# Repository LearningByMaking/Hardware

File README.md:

# Hardware
The design files and documentation for the LbyM hardware

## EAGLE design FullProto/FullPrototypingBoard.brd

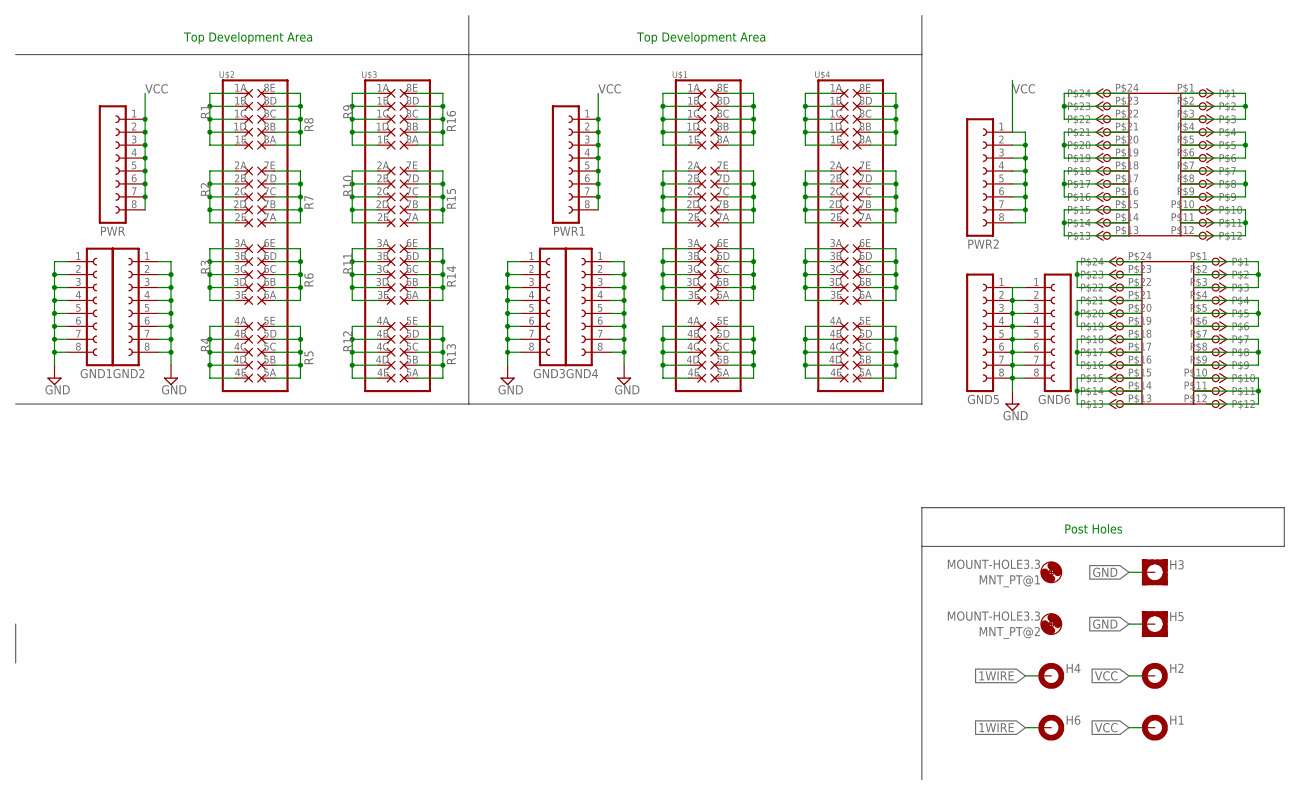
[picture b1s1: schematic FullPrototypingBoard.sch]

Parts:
GND1, GND2, GND3, GND4, GND5, GND6: FE08-GND
H1, H2, H4, H6: MOUNT-PAD-ROUND3.3; 3,3-PAD
H3, H5: MOUNT-PAD-SQUARE3.3; 3,3-PAD-SQUARE
MNT_PT@1, MNT_PT@2: MOUNT-HOLE3.3; 3,3
PWR, PWR1, PWR2: FE08
U$1, U$2, U$3, U$4: PROTO-5X8; PROTO-5X08
U$5, U$6: PROTO-3X8; PROTO-3X08

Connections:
1WIRE: H4.B3,3, H6.B3,3
GND: GND1.1, GND1.2, GND1.3, GND1.4, GND1.5, GND1.6, GND1.7, GND1.8, GND2.1, GND2.2, GND2.3, GND2.4, GND2.5, GND2.6, GND2.7, GND2.8, GND3.1, GND3.2, GND3.3, GND3.4, GND3.5, GND3.6, GND3.7, GND3.8, GND4.1, GND4.2, GND4.3, GND4.4, GND4.5, GND4.6, GND4.7, GND4.8, GND5.1, GND5.2, GND5.3, GND5.4, GND5.5, GND5.6, GND5.7, GND5.8, GND6.1, GND6.2, GND6.3, GND6.4, GND6.5, GND6.6, GND6.7, GND6.8, H3.B3,3, H5.B3,3
unnamed: U$5.P$22, U$5.P$23, U$5.P$24
unnamed: U$5.P$19, U$5.P$20, U$5.P$21
unnamed: U$5.P$16, U$5.P$17, U$5.P$18
unnamed: U$5.P$13, U$5.P$14, U$5.P$15
unnamed: U$5.P$1, U$5.P$2, U$5.P$3
unnamed: U$5.P$4, U$5.P$5, U$5.P$6
unnamed: U$5.P$7, U$5.P$8, U$5.P$9
unnamed: U$5.P$10, U$5.P$11
unnamed: U$6.P$22, U$6.P$23, U$6.P$24
unnamed: U$6.P$19, U$6.P$20, U$6.P$21
unnamed: U$6.P$16, U$6.P$17, U$6.P$18
unnamed: U$6.P$13, U$6.P$14, U$6.P$15
unnamed: U$6.P$1, U$6.P$2, U$6.P$3
unnamed: U$6.P$4, U$6.P$5, U$6.P$6
unnamed: U$6.P$7, U$6.P$8, U$6.P$9
unnamed: U$6.P$10, U$6.P$11
unnamed: U$1.1A, U$1.1B, U$1.1C, U$1.1D, U$1.1E
unnamed: U$1.8A, U$1.8B, U$1.8C, U$1.8D, U$1.8E
unnamed: U$1.7A, U$1.7B, U$1.7C, U$1.7D, U$1.7E
unnamed: U$1.2A, U$1.2B, U$1.2C, U$1.2D, U$1.2E
unnamed: U$1.6A, U$1.6B, U$1.6C, U$1.6D, U$1.6E
unnamed: U$1.3A, U$1.3B, U$1.3C, U$1.3D, U$1.3E
unnamed: U$1.5A, U$1.5B, U$1.5C, U$1.5D, U$1.5E
unnamed: U$1.4A, U$1.4B, U$1.4C, U$1.4D, U$1.4E
unnamed: U$4.8A, U$4.8B, U$4.8C, U$4.8D, U$4.8E
unnamed: U$4.1A, U$4.1B, U$4.1C, U$4.1D, U$4.1E
unnamed: U$4.7A, U$4.7B, U$4.7C, U$4.7D, U$4.7E
unnamed: U$4.2A, U$4.2B, U$4.2C, U$4.2D, U$4.2E
unnamed: U$4.6A, U$4.6B, U$4.6C, U$4.6D, U$4.6E
unnamed: U$4.3A, U$4.3B, U$4.3C, U$4.3D, U$4.3E
unnamed: U$4.5A, U$4.5B, U$4.5C, U$4.5D, U$4.5E
unnamed: U$4.4A, U$4.4B, U$4.4C, U$4.4D, U$4.4E
R1: U$2.1A, U$2.1B, U$2.1C, U$2.1D, U$2.1E
R2: U$2.2A, U$2.2B, U$2.2C, U$2.2D, U$2.2E
R3: U$2.3A, U$2.3B, U$2.3C, U$2.3D, U$2.3E
R4: U$2.4A, U$2.4B, U$2.4C, U$2.4D, U$2.4E
R5: U$2.5A, U$2.5B, U$2.5C, U$2.5D, U$2.5E
R6: U$2.6A, U$2.6B, U$2.6C, U$2.6D, U$2.6E
R7: U$2.7A, U$2.7B, U$2.7C, U$2.7D, U$2.7E
R8: U$2.8A, U$2.8B, U$2.8C, U$2.8D, U$2.8E
R9: U$3.1A, U$3.1B, U$3.1C, U$3.1D, U$3.1E
R10: U$3.2A, U$3.2B, U$3.2C, U$3.2D, U$3.2E
R11: U$3.3A, U$3.3B, U$3.3C, U$3.3D, U$3.3E
R12: U$3.4A, U$3.4B, U$3.4C, U$3.4D, U$3.4E
R13: U$3.5A, U$3.5B, U$3.5C, U$3.5D, U$3.5E
R14: U$3.6A, U$3.6B, U$3.6C, U$3.6D, U$3.6E
R15: U$3.7A, U$3.7B, U$3.7C, U$3.7D, U$3.7E
R16: U$3.8A, U$3.8B, U$3.8C, U$3.8D, U$3.8E
VCC: H1.B3,3, H2.B3,3, PWR.1, PWR.2, PWR.3, PWR.4, PWR.5, PWR.6, PWR.7, PWR.8, PWR1.1, PWR1.2, PWR1.3, PWR1.4, PWR1.5, PWR1.6, PWR1.7, PWR1.8, PWR2.1, PWR2.2, PWR2.3, PWR2.4, PWR2.5, PWR2.6, PWR2.7, PWR2.8

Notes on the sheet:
Post Holes
Top Development Area

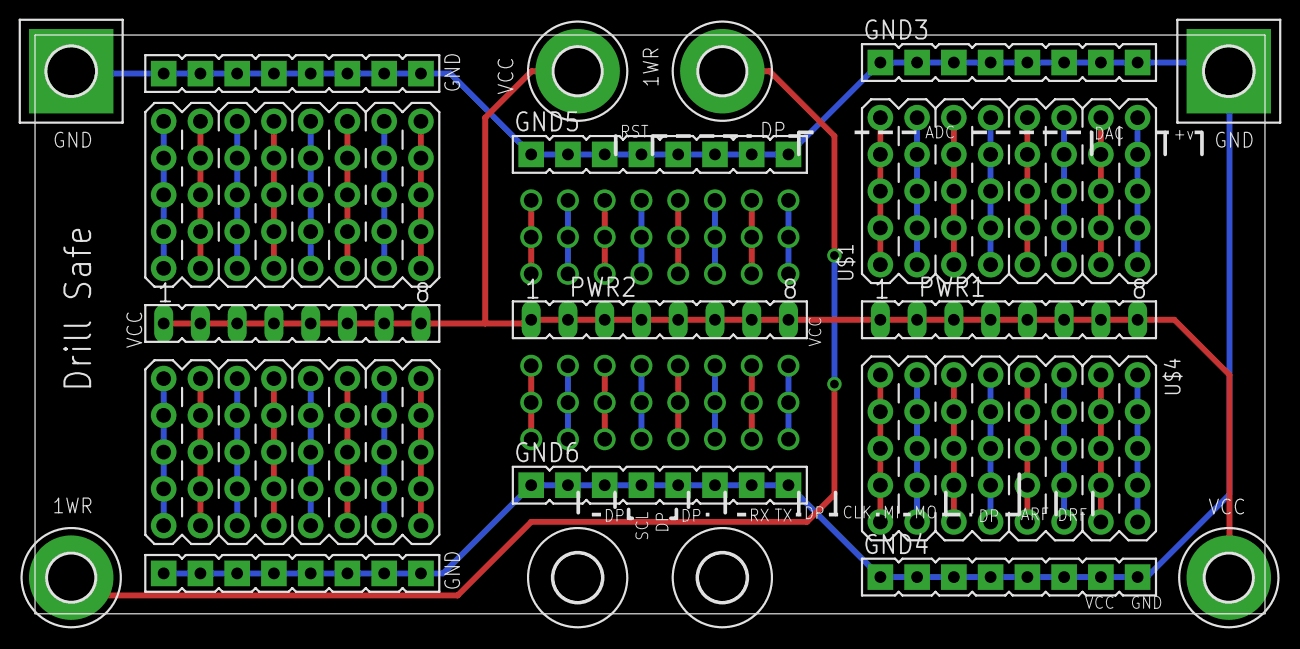
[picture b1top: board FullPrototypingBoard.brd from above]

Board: 2 copper layers, 85.0 x 40.0 mm, 23 parts (0 on the bottom side), 51 nets.

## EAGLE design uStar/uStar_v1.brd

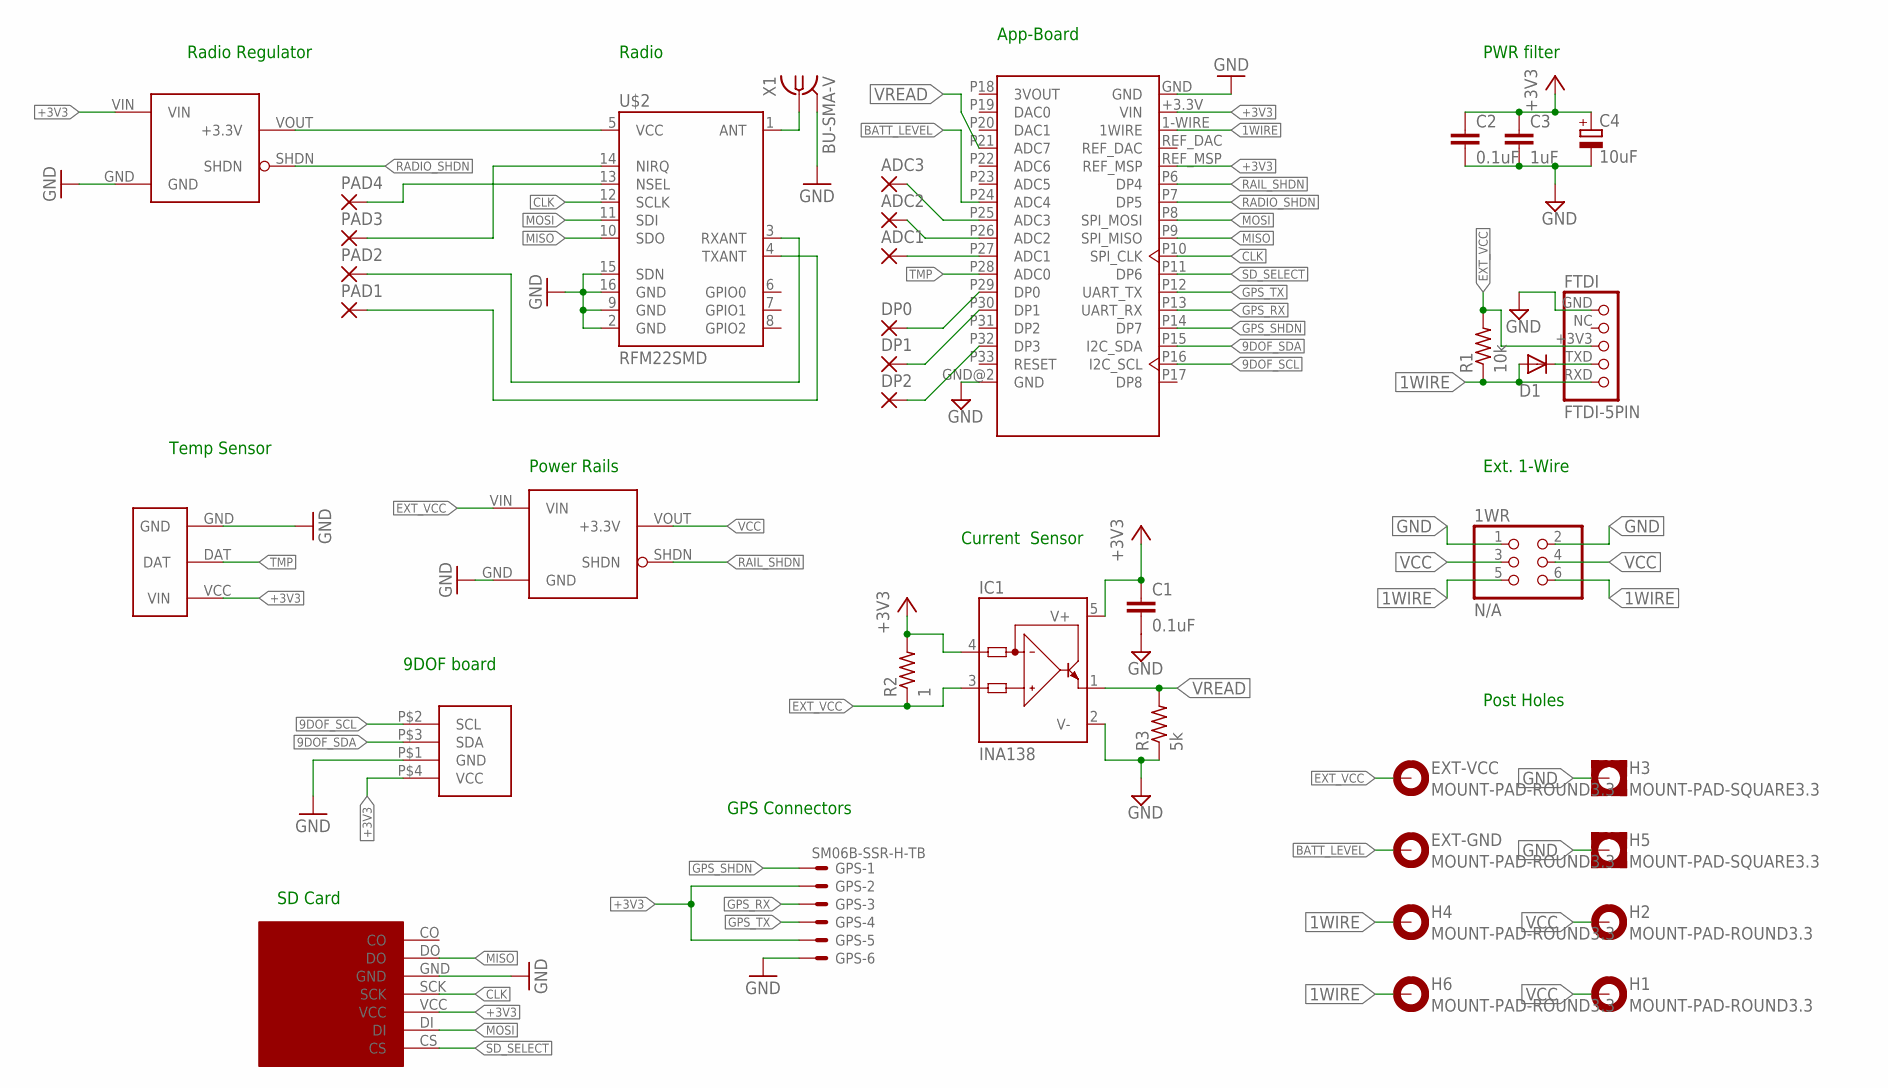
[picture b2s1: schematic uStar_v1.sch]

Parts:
1WR: N/A; 2X03
ADC1, ADC2, ADC3: 1,6/0,9
C1: 0.1uF; C0805
C2: 0.1uF; C0603
C3: 1uF; C0603
C4: 10uF; SMC_B
D1: 1N4148DO35-7; DO35-7
DP0, DP1, DP2: 1,6/0,9
EXT-GND: MOUNT-PAD-ROUND3.3; 3,3-PAD
EXT-VCC: MOUNT-PAD-ROUND3.3; 3,3-PAD
FTDI: FTDI-5PIN; 1_05X2MM
GPS: SM06B-SSR-H-TB
H1, H2, H4, H6: MOUNT-PAD-ROUND3.3; 3,3-PAD
H3, H5: MOUNT-PAD-SQUARE3.3; 3,3-PAD-SQUARE
IC1: INA138; SOT23-5
PAD1, PAD2, PAD3, PAD4: 1,6/0,9
R1: 10k; 0207/7
R2: 1; R0603
R3: 5k; R0603
U$1: App-Board 1.2/1.3; APPCORE_RECEIVER
U$2: RFM22SMD; RFM22-XXX-S2
U$3, U$7: S7V8F3_VOLT_REG-3V3_1AHORZ-DOWN; S7V_DOWN
U$4: TMP_EXT
U$5: 9DOF
U$6: BOB-00544
X1: BU-SMA-V

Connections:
1WIRE: 1WR.5, 1WR.6, D1.A, FTDI.RXD, H4.B3,3, H6.B3,3, R1.1, U$1.1-WIRE (1WIRE)
9DOF_SCL: U$1.P16 (I2C_SCL), U$5.P$2 (SCL)
9DOF_SDA: U$1.P15 (I2C_SDA), U$5.P$3 (SDA)
BATT_LEVEL: EXT-GND.B3,3, U$1.P24 (ADC4)
CLK: U$1.P10 (SPI_CLK), U$2.12 (SCLK), U$6.SCK
GND: 1WR.1, 1WR.2, C1.2, C2.2, C3.2, C4.-, FTDI.GND, GPS.6, H3.B3,3, H5.B3,3, IC1.2 (V-), R3.1, U$1.GND, U$1.GND@2 (GND), U$2.2 (GND), U$2.9 (GND), U$2.15 (SDN), U$2.16 (GND), U$3.GND, U$4.GND, U$5.P$1 (GND), U$6.GND, U$7.GND, X1.2, X1.3 (2), X1.4 (2), X1.5 (2); also elsewhere on the board
GPS_RX: GPS.3, U$1.P13 (UART_RX)
GPS_SHDN: GPS.1, U$1.P14 (DP7)
GPS_TX: GPS.4, U$1.P12 (UART_TX)
MISO: U$1.P9 (SPI_MISO), U$2.10 (SDO), U$6.DO
MOSI: U$1.P8 (SPI_MOSI), U$2.11 (SDI), U$6.DI
unnamed: PAD1.1, U$2.4 (TXANT)
unnamed: PAD2.1, U$2.3 (RXANT)
unnamed: D1.C, FTDI.TXD
unnamed: PAD3.1, U$2.14 (NIRQ)
unnamed: PAD4.1, U$2.13 (NSEL)
unnamed: U$2.1 (ANT), X1.1
unnamed: U$2.5 (VCC), U$3.VOUT (+3.3V)
unnamed: ADC1.1, U$1.P27 (ADC1)
unnamed: ADC2.1, U$1.P26 (ADC2)
unnamed: ADC3.1, U$1.P25 (ADC3)
unnamed: DP0.1, U$1.P29 (DP0)
unnamed: DP1.1, U$1.P30 (DP1)
unnamed: DP2.1, U$1.P32 (DP3)
RADIO_SHDN: U$1.P7 (DP5), U$3.SHDN; also elsewhere on the board
RAIL_SHDN: U$1.P6 (DP4), U$7.SHDN; also elsewhere on the board
SD_SELECT: U$1.P11 (DP6), U$6.CS
TMP: U$1.P28 (ADC0), U$4.DAT
VCC: 1WR.3, 1WR.4, H1.B3,3, H2.B3,3, U$7.VOUT (+3.3V)
VREAD: IC1.1 (OUT), R3.2, U$1.P21 (ADC7)

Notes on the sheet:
Post Holes
Ext. 1-Wire
App-Board
PWR filter
Current Sensor
Radio
Radio Regulator
Temp Sensor
9DOF board
GPS Connectors
SD Card
Power Rails

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
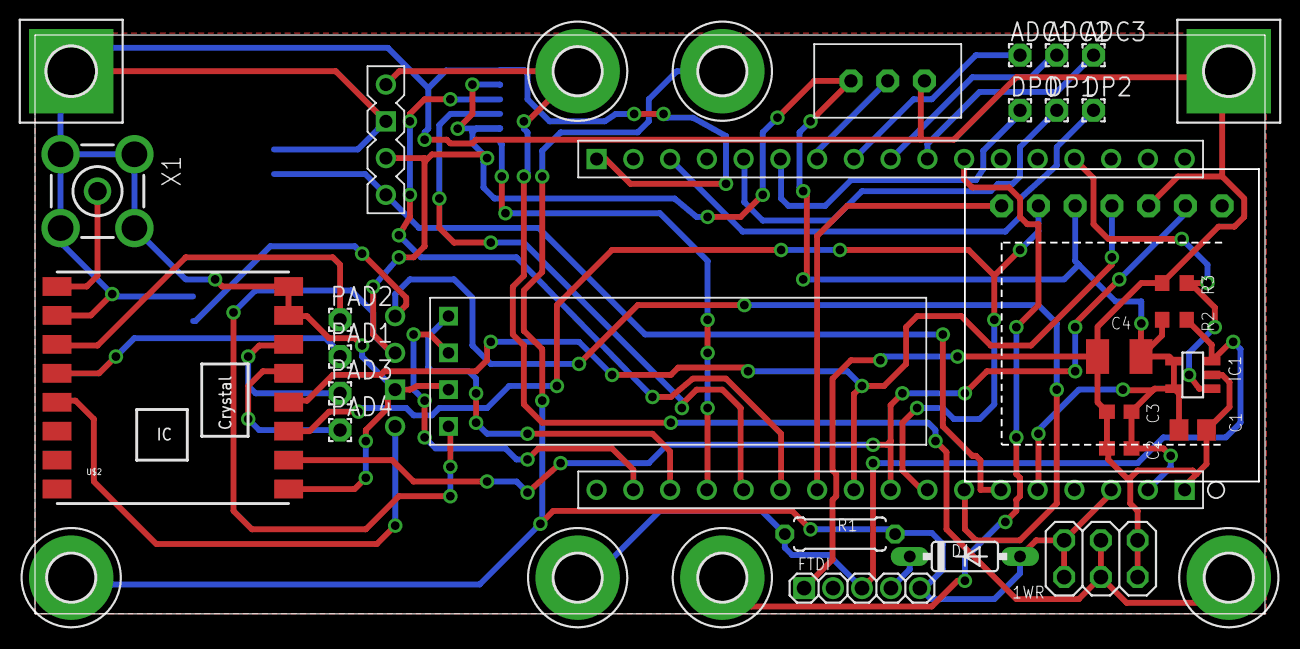
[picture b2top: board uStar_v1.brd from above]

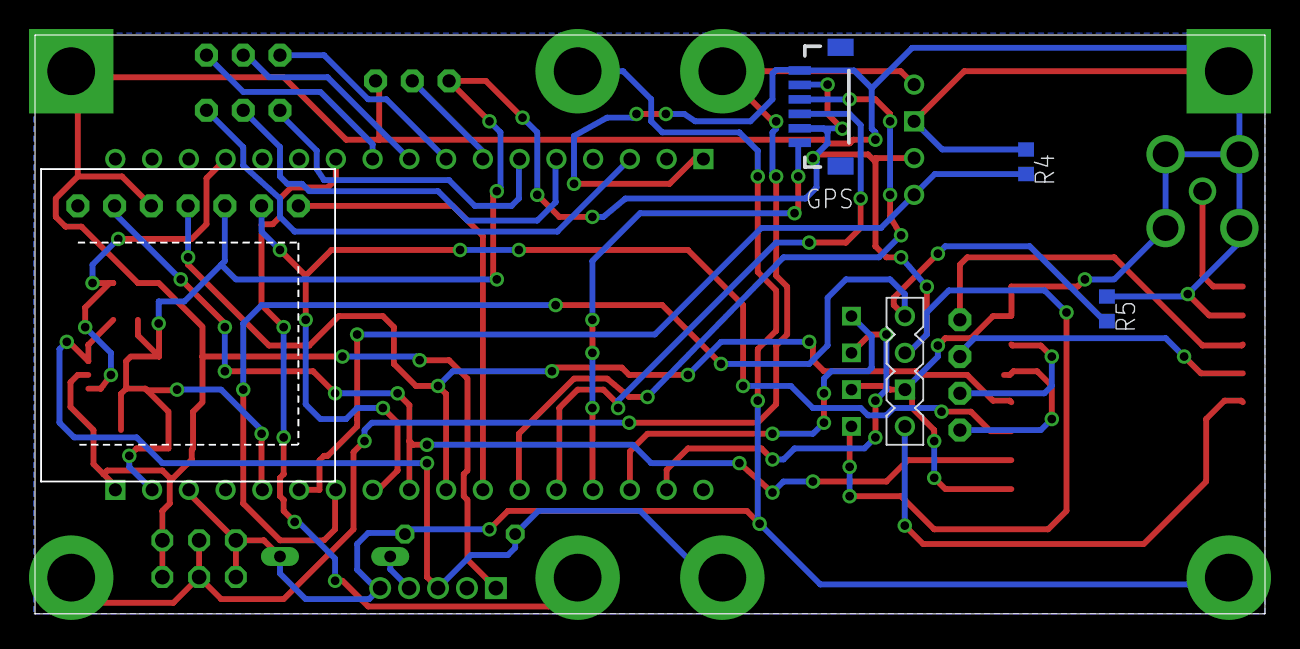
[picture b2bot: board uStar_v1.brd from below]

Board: 2 copper layers, 85.0 x 40.0 mm, 40 parts (5 on the bottom side), 32 nets.

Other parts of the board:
R4, R5: 50K; R0603

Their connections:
GND: R4.1, R5.1; also elsewhere on the board
RADIO_SHDN: R5.2; also elsewhere on the board
RAIL_SHDN: R4.2; also elsewhere on the board

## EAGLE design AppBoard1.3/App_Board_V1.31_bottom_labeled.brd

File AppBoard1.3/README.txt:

Hello potential App Board Assember,

In this document you should find:

2 PDF schematics documentating which SMD parts go where
1 parts list outlining all the parts used on the board
1 folder of images of the board both populated and unpopulated

Hopefully this is everything you need to construct an accurate bid/budget for the project. While the project focuses mainly on the surface mount components, please also include the soldering of all header pins in your estimate as well as the costs of properly packaging and shipping the completed boards back to Sonoma State. 

If you have any further technical questions, please do not hestitate to contact me directly:

Kevin John
(707) 664-3460
kj@universe.sonoma.edu

If you have any financial or administrative questions, please direct them to the sender of this email.

Thanks for your interest in the project, 
-Kevin

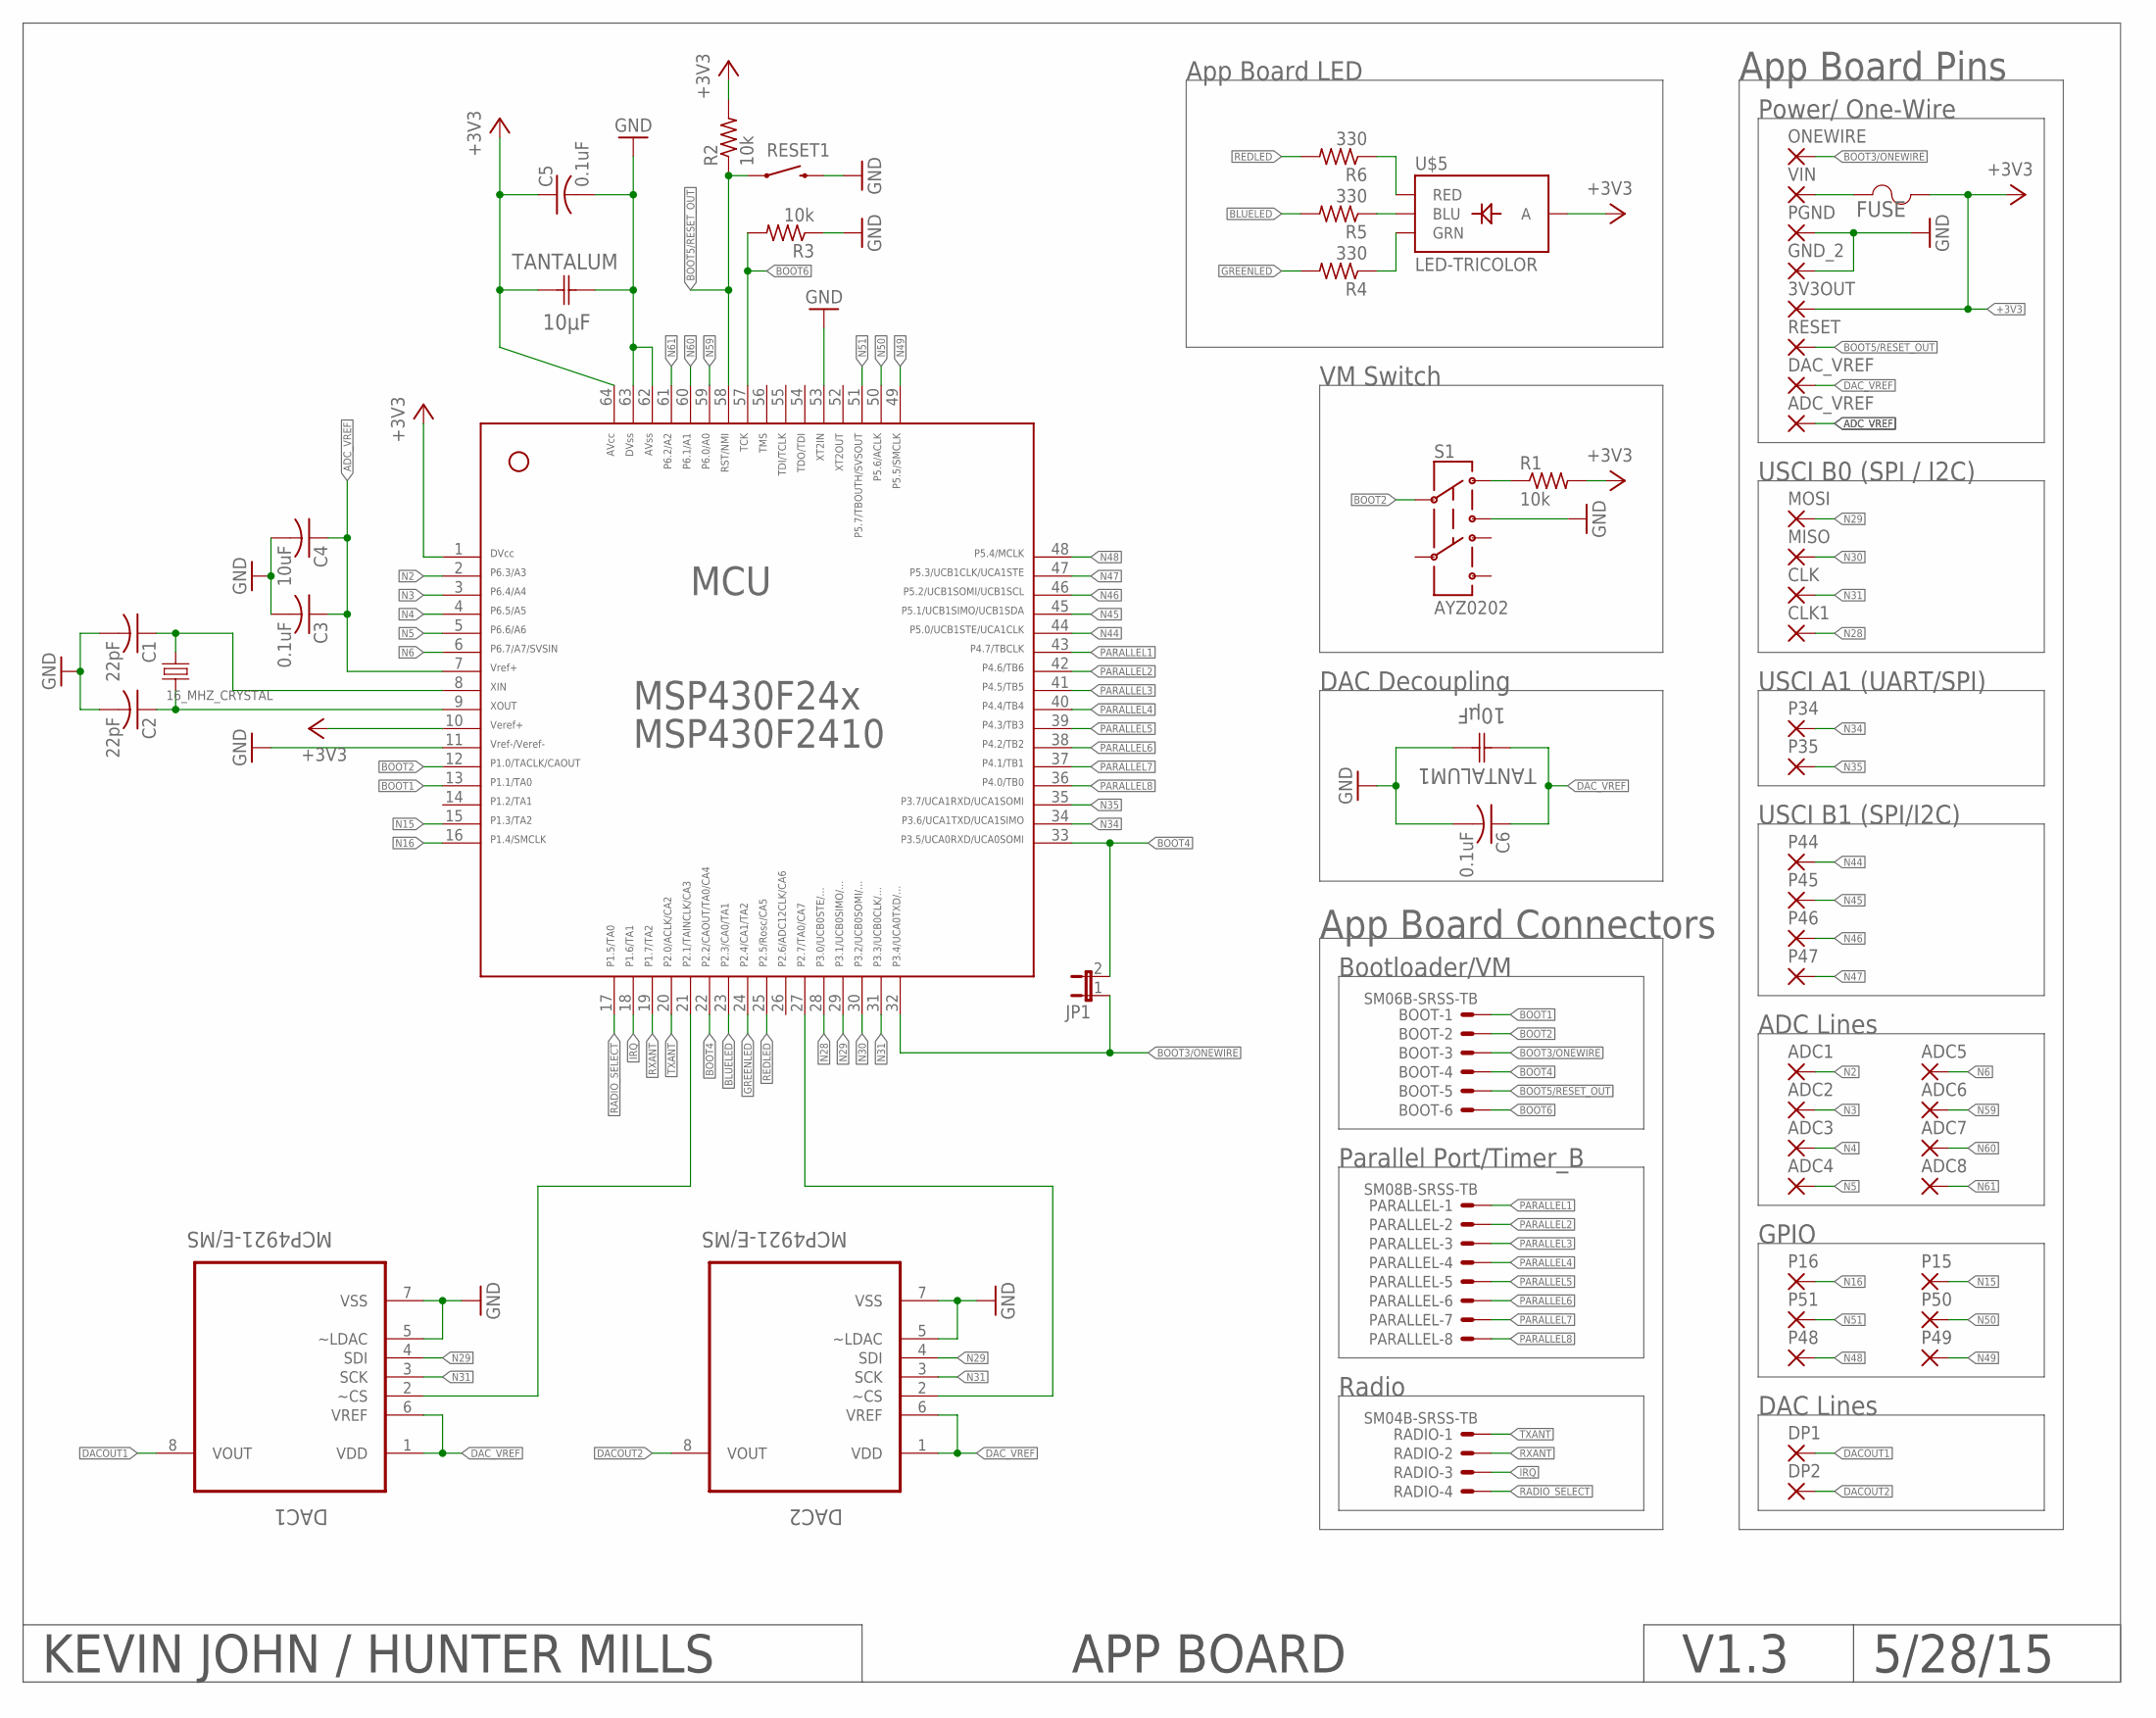
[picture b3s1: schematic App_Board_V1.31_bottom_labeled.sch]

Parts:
3V3OUT: 1,6/0,9
16_MHZ_CRYSTAL: HUNTERCRYSTAL; CRYSTAL-SMD-5X3
ADC1, ADC2, ADC3, ADC4, ADC5, ADC6, ADC7, ADC8: 1,6/0,9
ADC_VREF: 1,6/0,9
BOOT: SM06B-SRSS-TB
C1, C2: 22pF; C0805
C3, C5, C6: 0.1uF; C0805
C4: 10uF; C0805
CLK, CLK1: 1,6/0,9
DAC1, DAC2: MCP4921-E/MS; SOP65P490X110-8N
DAC_VREF: 1,6/0,9
DP1, DP2: 1,6/0,9
FUSE: HUNTERFUSE; CAPC4532X254N
GND_2: 1,6/0,9
JP1: JP1E; JP1
MCU: F24[X/10]---PM64; PM/PAG64
MISO: 1,6/0,9
MOSI: 1,6/0,9
ONEWIRE: 1,6/0,9
P15, P16, P34, P35, P44, P45, P46, P47, P48, P49, P50, P51: 1,6/0,9
PARALLEL: SM08B-SRSS-TB
PGND: 1,6/0,9
R1, R2, R3: 10k; R0603
R4, R5, R6: 330; R0603
RADIO: SM04B-SRSS-TB
RESET: 1,6/0,9
RESET1: SWITCH-MOMENTARY-2SMD; TACTILE-SWITCH-SMD
S1: AYZ0202
TANTALUM, TANTALUM1: 10µF; CAPCP3528X120N
U$5: LED-TRICOLOR; LED-TRICOLOR-SMD
VIN: 1,6/0,9

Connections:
3.3VOUT: FUSE.1, VIN.1
+3V3: 3V3OUT.1, C5.1, FUSE.2, MCU.1, MCU.10, MCU.64, R1.2, R2.2, TANTALUM.1 (C1), U$5.A
ADC_VREF: ADC_VREF.1, C3.1, C4.1, MCU.7
BLUELED: MCU.23, R5.2
BOOT1: BOOT.1, MCU.13
BOOT2: BOOT.2, MCU.12, S1.2
BOOT3/ONEWIRE: BOOT.3, JP1.1, MCU.32, ONEWIRE.1
BOOT4: BOOT.4, JP1.2, MCU.22, MCU.33
BOOT5/RESET_OUT: BOOT.5, MCU.58, R2.1, RESET.1, RESET1.1
BOOT6: BOOT.6, MCU.57, R3.2
DACOUT1: DAC1.8 (VOUT), DP1.1
DACOUT2: DAC2.8 (VOUT), DP2.1
DAC_VREF: C6.1, DAC1.1 (VDD), DAC1.6 (VREF), DAC2.1 (VDD), DAC2.6 (VREF), DAC_VREF.1, TANTALUM1.1 (C1)
GND: C1.2, C2.2, C3.2, C4.2, C5.2, C6.2, DAC1.5 (~LDAC), DAC1.7 (VSS), DAC2.5 (~LDAC), DAC2.7 (VSS), GND_2.1, MCU.11, MCU.53, MCU.62, MCU.63, PGND.1, R3.1, RESET1.3 (2), S1.1 (3), TANTALUM.2 (C2), TANTALUM1.2 (C2)
GREENLED: MCU.24, R4.2
IRQ: MCU.18, RADIO.3
N2: ADC1.1, MCU.2
N3: ADC2.1, MCU.3
N4: ADC3.1, MCU.4
N5: ADC4.1, MCU.5
N6: ADC5.1, MCU.6
N15: MCU.15, P15.1
N16: MCU.16, P16.1
N28: CLK1.1, MCU.28
N29: DAC1.4 (SDI), DAC2.4 (SDI), MCU.29, MOSI.1
N30: MCU.30, MISO.1
N31: CLK.1, DAC1.3 (SCK), DAC2.3 (SCK), MCU.31
N34: MCU.34, P34.1
N35: MCU.35, P35.1
N44: MCU.44, P44.1
N45: MCU.45, P45.1
N46: MCU.46, P46.1
N47: MCU.47, P47.1
N48: MCU.48, P48.1
N49: MCU.49, P49.1
N50: MCU.50, P50.1
N51: MCU.51, P51.1
N59: ADC6.1, MCU.59
N60: ADC7.1, MCU.60
N61: ADC8.1, MCU.61
unnamed: 16_MHZ_CRYSTAL.3, C1.1, MCU.8
unnamed: 16_MHZ_CRYSTAL.1, C2.1, MCU.9
unnamed: R1.1, S1.3 (1)
unnamed: R5.1, U$5.B (BLU)
unnamed: R6.1, U$5.R (RED)
unnamed: R4.1, U$5.G (GRN)
unnamed: DAC1.2 (~CS), MCU.21
unnamed: DAC2.2 (~CS), MCU.27
PARALLEL1: MCU.43, PARALLEL.1
PARALLEL2: MCU.42, PARALLEL.2
PARALLEL3: MCU.41, PARALLEL.3
PARALLEL4: MCU.40, PARALLEL.4
PARALLEL5: MCU.39, PARALLEL.5
PARALLEL6: MCU.38, PARALLEL.6
PARALLEL7: MCU.37, PARALLEL.7
PARALLEL8: MCU.36, PARALLEL.8
RADIO_SELECT: MCU.17, RADIO.4
REDLED: MCU.25, R6.2
RXANT: MCU.19, RADIO.2
TXANT: MCU.20, RADIO.1

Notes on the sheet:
KEVIN JOHN / HUNTER MILLS
APP BOARD
V1.3
5/28/15
Power/ One-Wire
ADC Lines
DAC Lines
USCI B0 (SPI / I2C)
USCI A1 (UART/SPI)
USCI B1 (SPI/I2C)
GPIO
App Board Pins
Bootloader/VM
Parallel Port/Timer_B
Radio
App Board Connectors
App Board LED
VM Switch
DAC Decoupling

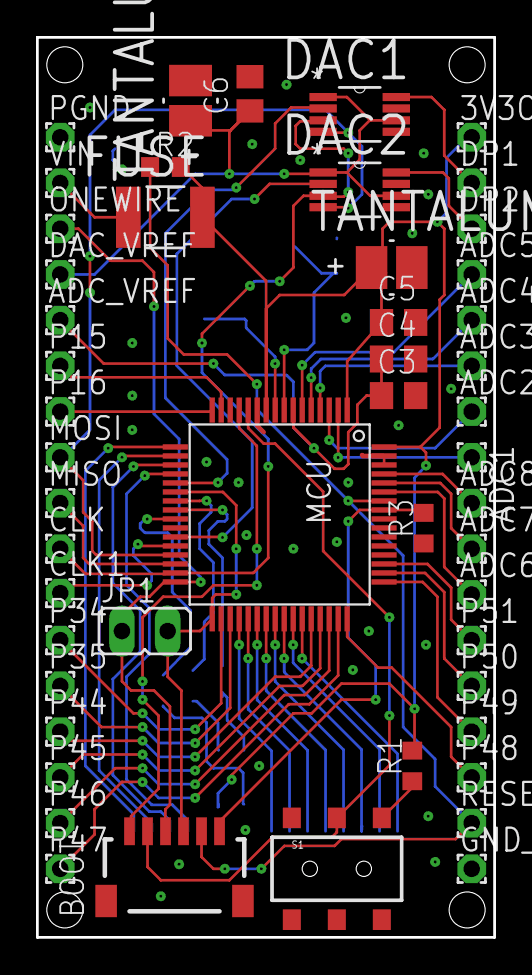
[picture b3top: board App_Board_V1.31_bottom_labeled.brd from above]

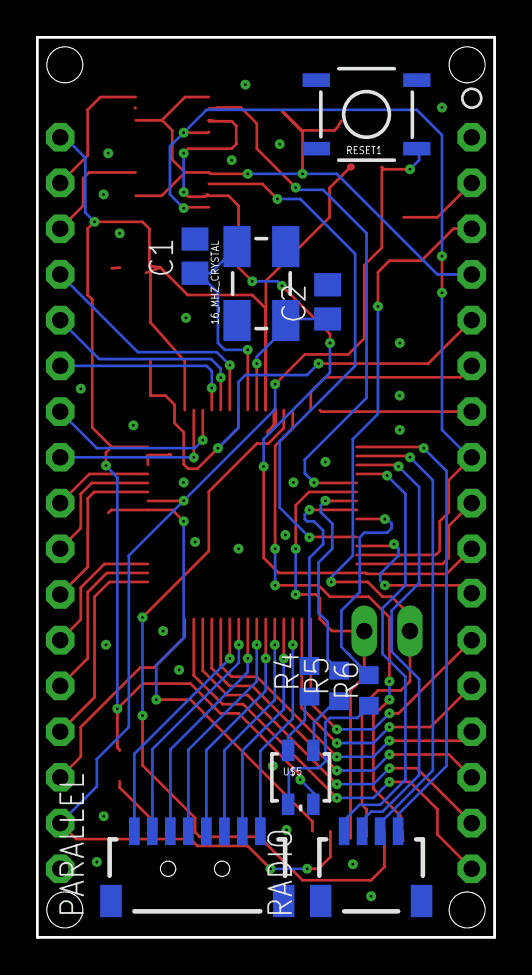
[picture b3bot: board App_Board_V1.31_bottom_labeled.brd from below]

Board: 2 copper layers, 25.4 x 50.0 mm, 60 parts (10 on the bottom side), 60 nets.

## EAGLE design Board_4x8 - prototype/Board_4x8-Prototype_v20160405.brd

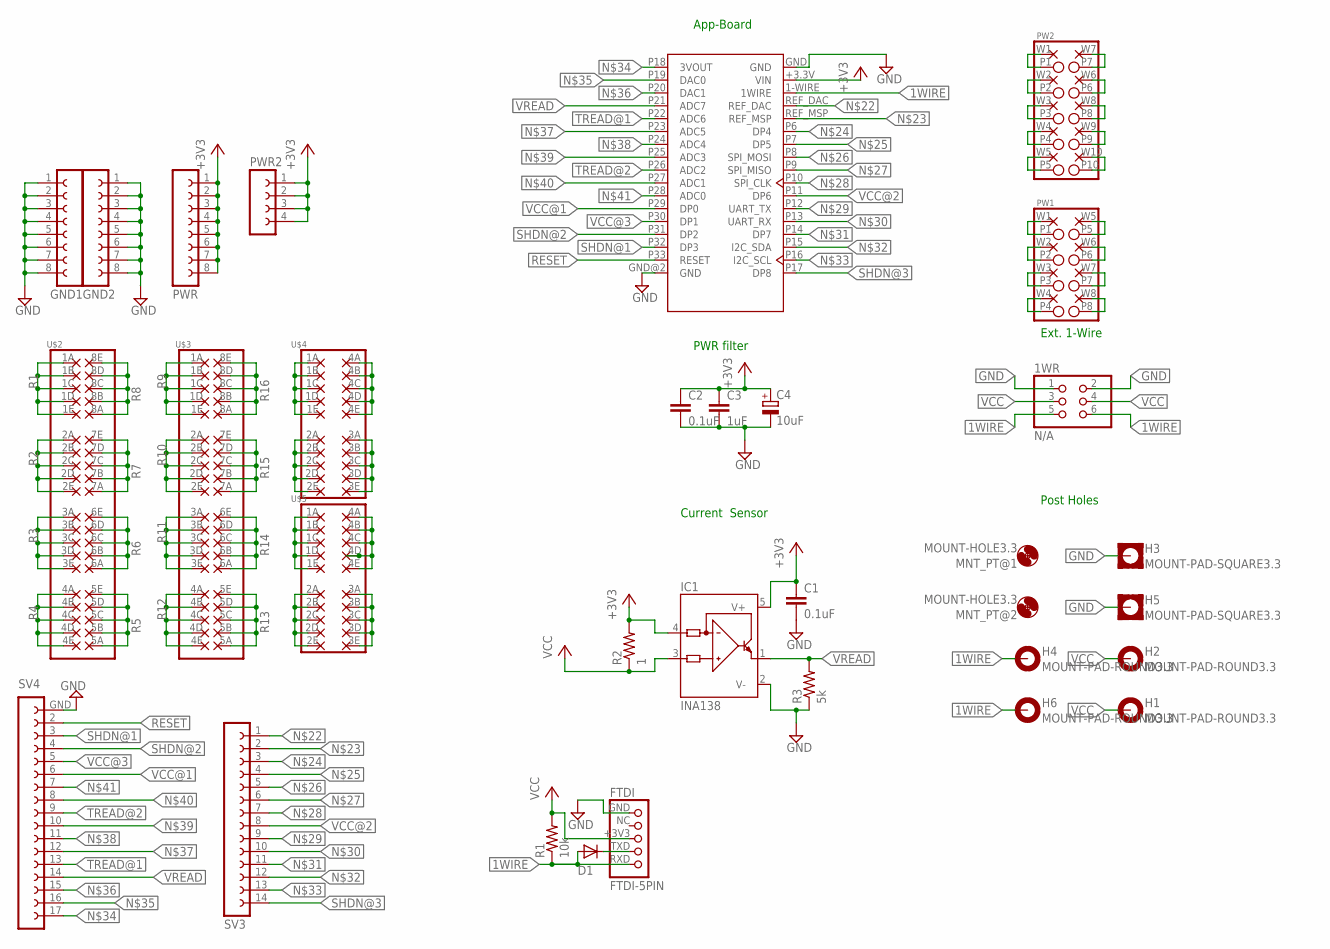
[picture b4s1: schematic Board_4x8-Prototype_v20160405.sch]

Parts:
1WR: N/A; 2X03
C1: 0.1uF; C0805
C2: 0.1uF; C0603
C3: 1uF; C0603
C4: 10uF; SMC_B
D1: 1N4148DO35-7; DO35-7
FTDI: FTDI-5PIN; 1_05X2MM
GND1, GND2: FE08-GND
H1, H2, H4, H6: MOUNT-PAD-ROUND3.3; 3,3-PAD
H3, H5: MOUNT-PAD-SQUARE3.3; 3,3-PAD-SQUARE
IC1: INA138; SOT23-5
MNT_PT@1, MNT_PT@2: MOUNT-HOLE3.3; 3,3
PW1: PIN-WIRE-2X8; 2X8
PW2: PIN-WIRE-2X10; 2X10
PWR: FE08
PWR2: FE04-1
R1: 10k; 0207/7
R2: 1; R0603
R3: 5k; R0603
SV3: FE14-1_ABBO
SV4: FE17-1_ABBO
U$1: App-Board 1.2/1.3; APPCORE_RECEIVER
U$2, U$3: PROTO-5X8; PROTO-2X05
U$4, U$5: PROTO-4X5; PROTO-4X05

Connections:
1WIRE: 1WR.5, 1WR.6, D1.A, FTDI.RXD, H4.B3,3, H6.B3,3, R1.1, U$1.1-WIRE (1WIRE)
+3V3: C1.1, C2.1, C3.1, C4.+, IC1.4 (IN-), IC1.5 (V+), PWR.1, PWR.2, PWR.3, PWR.4, PWR.5, PWR.6, PWR.7, PWR.8, PWR2.1, PWR2.2, PWR2.3, PWR2.4, R2.2, U$1.+3.3V (VIN)
GND: 1WR.1, 1WR.2, C1.2, C2.2, C3.2, C4.-, FTDI.GND, GND1.1, GND1.2, GND1.3, GND1.4, GND1.5, GND1.6, GND1.7, GND1.8, GND2.1, GND2.2, GND2.3, GND2.4, GND2.5, GND2.6, GND2.7, GND2.8, H3.B3,3, H5.B3,3, IC1.2 (V-), R3.1, SV4.GND, U$1.GND, U$1.GND@2 (GND)
unnamed: U$4.1A, U$4.1B, U$4.1C, U$4.1D, U$4.1E
unnamed: PW1.P1, PW1.W1
unnamed: D1.C, FTDI.TXD
unnamed: PW1.P2, PW1.W2
unnamed: U$4.4A, U$4.4B, U$4.4C, U$4.4D, U$4.4E
unnamed: U$4.2A, U$4.2B, U$4.2C, U$4.2D, U$4.2E
unnamed: U$4.3A, U$4.3B, U$4.3C, U$4.3D, U$4.3E
unnamed: U$5.1A, U$5.1B, U$5.1C, U$5.1D, U$5.1E
unnamed: U$5.4A, U$5.4B, U$5.4C, U$5.4D, U$5.4E
unnamed: U$5.2A, U$5.2B, U$5.2C, U$5.2D, U$5.2E
unnamed: U$5.3A, U$5.3B, U$5.3C, U$5.3D, U$5.3E
unnamed: PW2.P1, PW2.W1
unnamed: PW2.P2, PW2.W2
unnamed: PW2.P3, PW2.W3
unnamed: PW2.P4, PW2.W4
unnamed: PW2.P5, PW2.W5
unnamed: PW2.P7, PW2.W7
unnamed: PW2.P6, PW2.W6
unnamed: PW2.P8, PW2.W8
unnamed: PW2.P9, PW2.W9
unnamed: PW2.P10, PW2.W10
unnamed: SV3.1, U$1.REF_DAC
unnamed: SV3.2, U$1.REF_MSP
unnamed: SV3.3, U$1.P6 (DP4)
unnamed: SV3.4, U$1.P7 (DP5)
unnamed: SV3.5, U$1.P8 (SPI_MOSI)
unnamed: SV3.6, U$1.P9 (SPI_MISO)
unnamed: SV3.7, U$1.P10 (SPI_CLK)
unnamed: SV3.9, U$1.P12 (UART_TX)
unnamed: SV3.10, U$1.P13 (UART_RX)
unnamed: SV3.11, U$1.P14 (DP7)
unnamed: SV3.12, U$1.P15 (I2C_SDA)
unnamed: SV3.13, U$1.P16 (I2C_SCL)
unnamed: SV4.17, U$1.P18 (3VOUT)
unnamed: SV4.16, U$1.P19 (DAC0)
unnamed: SV4.15, U$1.P20 (DAC1)
unnamed: SV4.12, U$1.P23 (ADC5)
unnamed: SV4.11, U$1.P24 (ADC4)
unnamed: SV4.10, U$1.P25 (ADC3)
unnamed: SV4.8, U$1.P27 (ADC1)
unnamed: SV4.7, U$1.P28 (ADC0)
unnamed: PW1.P3, PW1.W3
unnamed: PW1.P4, PW1.W4
unnamed: PW1.P5, PW1.W5
unnamed: PW1.P6, PW1.W6
unnamed: PW1.P7, PW1.W7
unnamed: PW1.P8, PW1.W8
R1: U$2.1A, U$2.1B, U$2.1C, U$2.1D, U$2.1E
R2: U$2.2A, U$2.2B, U$2.2C, U$2.2D, U$2.2E
R3: U$2.3A, U$2.3B, U$2.3C, U$2.3D, U$2.3E
R4: U$2.4A, U$2.4B, U$2.4C, U$2.4D, U$2.4E
R5: U$2.5A, U$2.5B, U$2.5C, U$2.5D, U$2.5E
R6: U$2.6A, U$2.6B, U$2.6C, U$2.6D, U$2.6E
R7: U$2.7A, U$2.7B, U$2.7C, U$2.7D, U$2.7E
R8: U$2.8A, U$2.8B, U$2.8C, U$2.8D, U$2.8E
R9: U$3.1A, U$3.1B, U$3.1C, U$3.1D, U$3.1E
R10: U$3.2A, U$3.2B, U$3.2C, U$3.2D, U$3.2E
R11: U$3.3A, U$3.3B, U$3.3C, U$3.3D, U$3.3E
R12: U$3.4A, U$3.4B, U$3.4C, U$3.4D, U$3.4E
R13: U$3.5A, U$3.5B, U$3.5C, U$3.5D, U$3.5E
R14: U$3.6A, U$3.6B, U$3.6C, U$3.6D, U$3.6E
R15: U$3.7A, U$3.7B, U$3.7C, U$3.7D, U$3.7E
R16: U$3.8A, U$3.8B, U$3.8C, U$3.8D, U$3.8E
RESET: SV4.2, U$1.P33 (RESET)
SHDN@1: SV4.3, U$1.P32 (DP3)
SHDN@2: SV4.4, U$1.P31 (DP2)
SHDN@3: SV3.14, U$1.P17 (DP8)
TREAD@1: SV4.13, U$1.P22 (ADC6)
TREAD@2: SV4.9, U$1.P26 (ADC2)
VCC: 1WR.3, 1WR.4, FTDI.+3V3, H1.B3,3, H2.B3,3, IC1.3 (IN+), R1.2, R2.1
VCC@1: SV4.6, U$1.P29 (DP0)
VCC@2: SV3.8, U$1.P11 (DP6)
VCC@3: SV4.5, U$1.P30 (DP1)
VREAD: IC1.1 (OUT), R3.2, SV4.14, U$1.P21 (ADC7)

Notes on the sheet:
Post Holes
Ext. 1-Wire
App-Board
PWR filter
Current Sensor

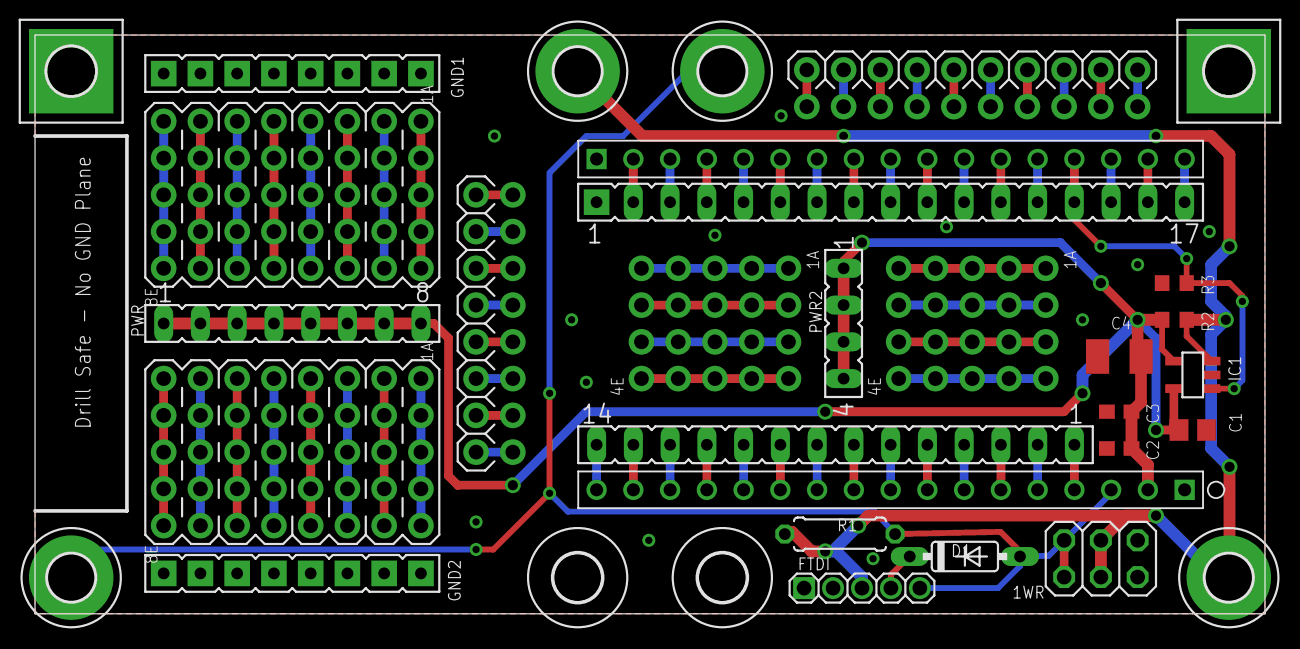
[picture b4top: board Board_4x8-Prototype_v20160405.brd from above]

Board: 2 copper layers, 85.0 x 40.0 mm, 32 parts (0 on the bottom side), 77 nets.

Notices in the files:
parts and their libraries:
SparkFun-Electromechanical: Licensing: CC v3.0 Share-Alike You are welcome to use this library for commercial purposes.
SparkFun-Electromechanical: Licensing: Creative Commons ShareAlike 4.0 International - https://creativecommons.org/licenses/by-sa/4.0
